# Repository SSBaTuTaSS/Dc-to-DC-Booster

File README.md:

# DC-DC Step-Up Converter

This project is a compact **DC-DC Boost Converter** design capable of stepping up an input voltage from **2.7V – 12V** to an output range of **4.5V – 14.7V**.  
The circuit is based on the TPS61288RQQR boost controller IC, designed in KiCad for PCB manufacturing.  

---

## 📐 Circuit Overview
- Input Voltage: 2.7V – 12V  
- Output Voltage: 4.5V – 14.7V (adjustable)  
- Controller IC: TPS61288RQQR (TI)  
- Output Current: 3A – 4A continuous, up to 6A peak
- Topology: Boost Converter  
- PCB Stackup: 2 Layers (FR4)  
- Key Components: Inductor, fast diode, MOSFET, bypass capacitors, and adjustable potentiometer  
- Application: Prototyping, powering devices requiring higher voltage from low-voltage sources (battery, USB, etc.)

 ---

Specifications of Circuit

| Parameter        | Value                                  |
|------------------|----------------------------------------|
| Input Voltage    | 2.7V – 12V                             |
| Output Voltage   | 4.5V – 14.7V (Adj)                     |
| Controller IC    | TPS61288RQQR                           |
| Topology         | Boost Converter                        |
| Output Current   | 3A – 4A continuous, up to 6A peak |
| Efficiency       | ~85% (typical)                         |
| PCB Stackup      | 2-layer FR4                            |
| Frequency        | High frequency                         |

---

## 📐 KiCad Schematic
Below is the KiCad schematic for the DC-DC Booster circuit:

---

## 🖼️ PCB Layout
2D PCB layout generated in KiCad (**2-layer, FR4 substrate**):  

---

## 🎨 3D PCB View
3D model rendered with KiCad Viewer:  

---

## 📁 Files
- `DCtoDCboost.kicad_pro` → KiCad project file  
- `DCtoDCboost.kicad_pcb` → KiCad PCB layout (2-layer FR4 stackup)  
- `DCtoDCboost.sch` → KiCad schematic file  

---

## ⚡ Features
- Compact design  
- Adjustable output voltage    
- High-frequency switching allows the use of small inductors and capacitors  
- Suitable for prototyping and embedded systems  

⚠️ **Warning**: Ensure the output does not exceed the rating of your connected device.  

## 📜 License
This project is licensed under the **MIT License** – see the [LICENSE](LICENSE) file for details.

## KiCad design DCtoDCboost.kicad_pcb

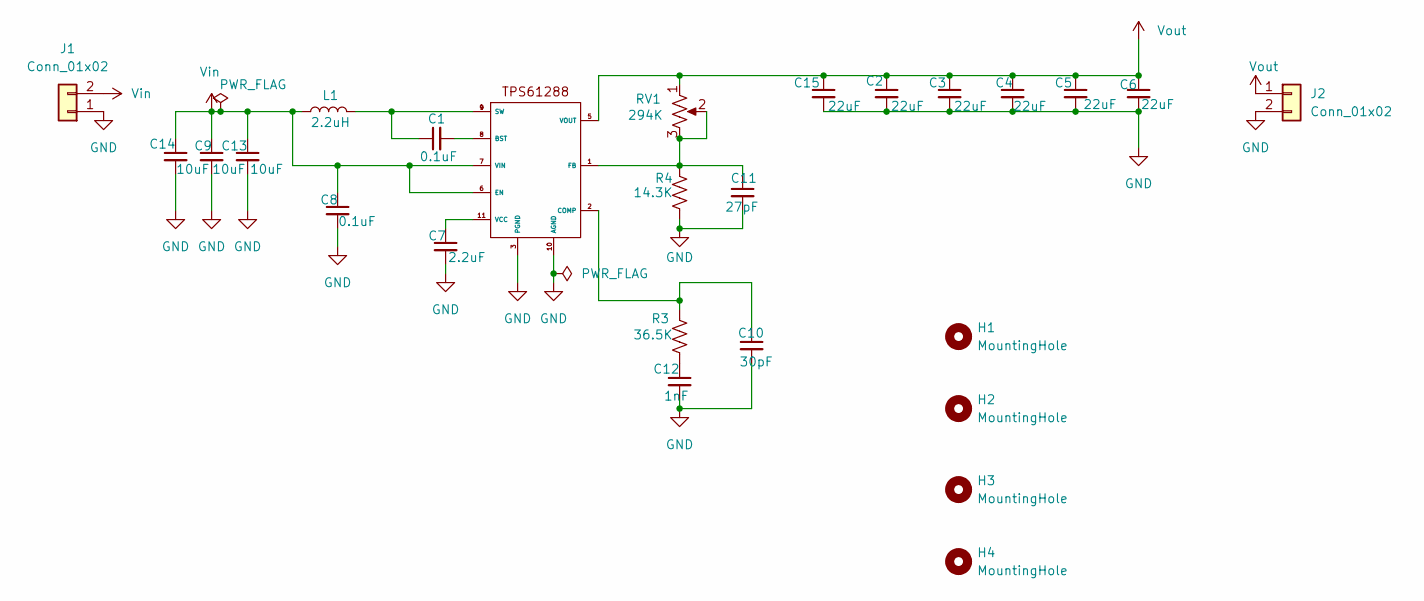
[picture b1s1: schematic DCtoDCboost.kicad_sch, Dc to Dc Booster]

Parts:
C1, C8: 0.1uF; C_0603_1608Metric
C2, C3, C4, C5, C6, C15: 22uF; C_1206_3216Metric
C7: 2.2uF; C_0805_2012Metric
C9, C13, C14: 10uF; C_0805_2012Metric
C10: 30pF; C_0603_1608Metric
C11: 27pF; C_0603_1608Metric
C12: 1nF; C_0603_1608Metric
H1, H2, H3, H4: MountingHole; MountingHole_2.2mm_M2_DIN965_Pad
J1, J2: Conn_01x02; PinHeader_1x02_P2.54mm_Vertical
L1: 2.2uH; IND_104CDMCCDS-2R2MC
R3: 36.5K; R_0603_1608Metric
R4: 14.3K; R_0603_1608Metric
RV1: 294K; TRIM_3362P-1-304LF
TPS1: CONV_TPS61288LRQQR

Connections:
GND: C2.2, C3.2, C4.2, C5.2, C6.2, C7.2, C8.2, C9.2, C10.2, C11.2, C12.2, C13.2, C14.2, C15.2, J1.1, J2.2, R4.2, TPS1.3 (PGND), TPS1.10 (AGND)
unnamed: C1.1, L1.2, TPS1.4 (SW), TPS1.9 (SW)
unnamed: C12.1, R3.2
unnamed: C1.2, TPS1.8 (BST)
unnamed: C10.1, R3.1, TPS1.2 (COMP)
unnamed: C11.1, R4.1, RV1.2, RV1.3, TPS1.1 (FB)
unnamed: C7.1, TPS1.11 (VCC)
Vin: C8.1, C9.1, C13.1, C14.1, J1.2, L1.1, TPS1.6 (EN), TPS1.7 (VIN)
Vout: C2.1, C3.1, C4.1, C5.1, C6.1, C15.1, J2.1, RV1.1, TPS1.5 (VOUT)

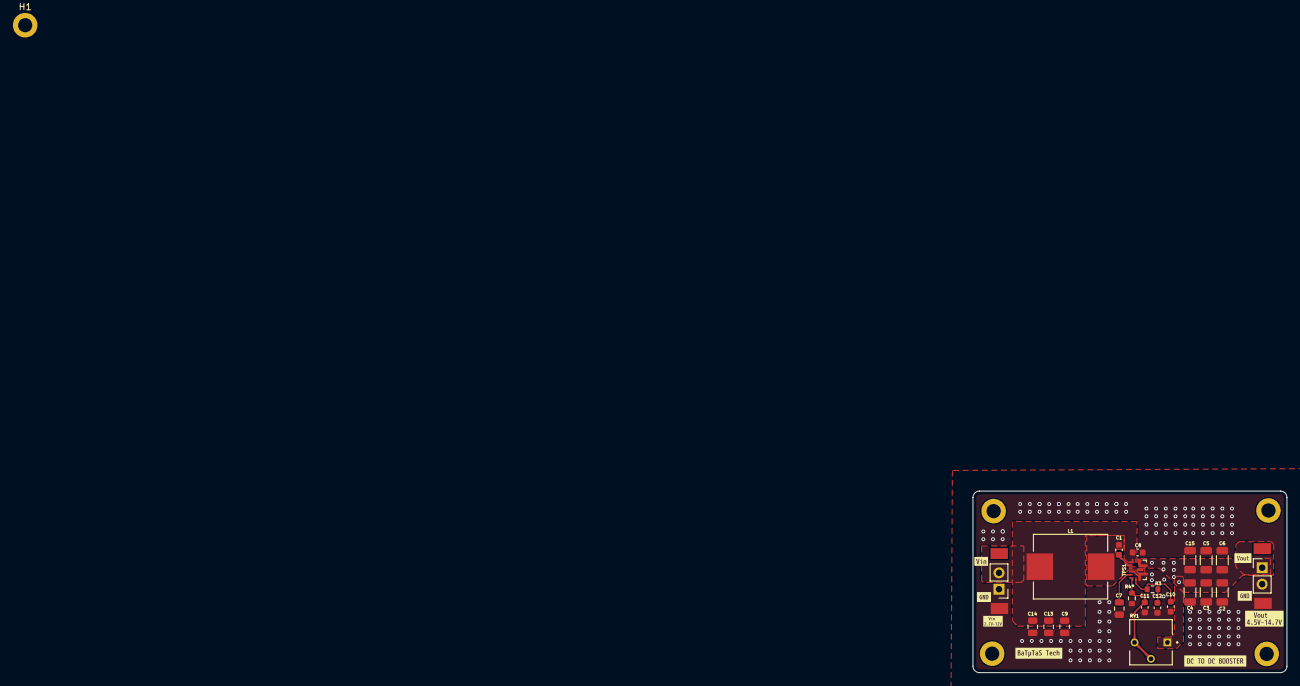
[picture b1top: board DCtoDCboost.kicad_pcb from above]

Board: 2 copper layers, 48.6 x 28.1 mm, 35 parts (0 on the bottom side), 9 nets.

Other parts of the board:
H1#2: MountingHole; MountingHole_2.2mm_M2_DIN965_Pad
kibuzzard-68C90A12: G***; kibuzzard-68C90A12
kibuzzard-68C90A33: G***; kibuzzard-68C90A33
kibuzzard-68C90B1F: G***; kibuzzard-68C90B1F
kibuzzard-68C91D84: G***; kibuzzard-68C91D84
kibuzzard-68C91DA4: G***; kibuzzard-68C91DA4
kibuzzard-68C918EC: G***; kibuzzard-68C918EC
kibuzzard-68C91464: G***; kibuzzard-68C91464
kibuzzard-68C91755: G***; kibuzzard-68C91755

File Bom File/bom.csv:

"Reference","Qty","Value","DNP","Exclude from BOM","Exclude from Board","Footprint","Datasheet"
"C1,C8","2","0.1uF","","","","Capacitor_SMD:C_0603_1608Metric","https://content.kemet.com/datasheets/KEM_C1003_C0G_SMD.pdf"
"C2,C3,C4,C5,C6,C15","6","22uF","","","","Capacitor_SMD:C_1206_3216Metric","https://content.kemet.com/datasheets/KEM_C1002_X7R_SMD.pdf"
"C7","1","2.2uF","","","","Capacitor_SMD:C_0805_2012Metric","https://www.yageogroup.com/content/datasheet/asset/file/KEM_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"
"C9,C13,C14","3","10uF","","","","Capacitor_SMD:C_0805_2012Metric","https://www.yageogroup.com/content/datasheet/asset/file/KEM_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"
"C10","1","30pF","","","","Capacitor_SMD:C_0603_1608Metric","https://datasheets.kyocera-avx.com/600S.pdf"
"C11","1","27pF","","","","Capacitor_SMD:C_0603_1608Metric","https://www.johansondielectrics.com/search/pn-pdf/QSCP251Q27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"
"C12","1","1nF","","","","Capacitor_SMD:C_0603_1608Metric","https://www.yageogroup.com/content/datasheet/asset/file/KEM_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"
"H1,H2,H3,H4","4","MountingHole","","Excluded from BOM","","MountingHole:MountingHole_2.2mm_M2_DIN965_Pad","~"
"J1,J2","2","Conn_01x02","","","","Connector_PinHeader_2.54mm:PinHeader_1x02_P2.54mm_Vertical","~"
"L1","1","2.2uH","","","","TPS61288RQQR:IND_104CDMCCDS-2R2MC","https://products.sumida.com/products/pdf/104CDMCCDS.pdf"
"R3","1","36.5K","","","","Resistor_SMD:R_0603_1608Metric","https://industrial.panasonic.com/cdbs/www-data/pdf/RDA0000/A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"
"R4","1","14.3K","","","","Resistor_SMD:R_0603_1608Metric","https://www.seielect.com/catalog/sei-rmcf_rmcp.pdf"
"RV1","1","294K","","","","TPS61288RQQR:TRIM_3362P-1-304LF","https://www.bourns.com/docs/Product-Datasheets/3362.pdf"
"TPS1","1","~","","","","TPS61288RQQR:CONV_TPS61288LRQQR","https://www.ti.com/lit/ds/symlink/tps61288.pdf"

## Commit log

2025-09-17 zzzz
2025-09-18 README.md
2025-09-19 LICENSE
2025-09-19 .gitignore
2025-09-19 Untracked dosyaları takipten çıkardım ve .gitignore güncelledim
2025-09-19 Projede tüm dosyaları ekledim
